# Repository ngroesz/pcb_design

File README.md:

# pcb_design
circuit board designs

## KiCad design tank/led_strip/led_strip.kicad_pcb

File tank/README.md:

# tank tank tank
Tank!

## Pixart camera
The turret board requires a Pixart camera. This component cannot be purchased off-the-shelf. Others pioneered the reusage of this module and plenty of documentation exists on the Internet. The camera modules are sourced from Wii Remotes, which can still (as of 2021) be sourced from eBay for fairly cheap. Search for "Wii Remote For Parts". They can be found individually or in lots, they shouldn't be much more than $5/controller. Make sure they are original Wii Remotes, not third-party copies nor "Wii Motion Plus". The camera module is fairly easy to desolder, though take care to not pull the contacts from the module when removing from the board. There are a couple other cool bits on a Wii Remote board, including a vibration motor and a beefy capacitor. These days, though I tend to just pull the camera module and throw away the rest.

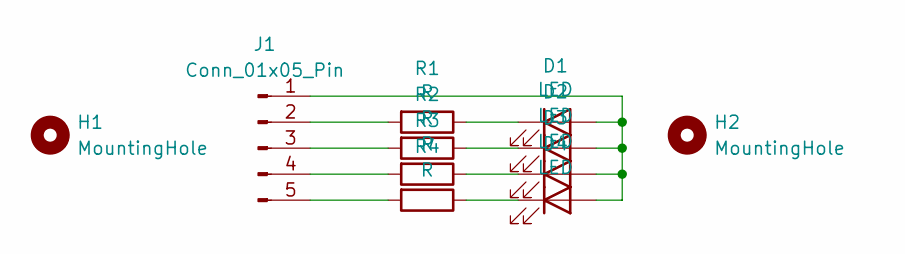
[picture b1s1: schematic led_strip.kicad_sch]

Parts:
D1, D2, D3, D4: LED; LED_D5.0mm
H1, H2: MountingHole; MountingHole_2.2mm_M2
J1: Conn_01x05_Pin; JST_XH_B5B-XH-A_1x05_P2.50mm_Vertical
R1, R2, R3, R4: R; R_Axial_DIN0207_L6.3mm_D2.5mm_P7.62mm_Horizontal

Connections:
unnamed: D1.2 (A), D2.2 (A), D3.2 (A), D4.2 (A), J1.1
unnamed: D1.1 (K), R1.1
unnamed: D2.1 (K), R2.1
unnamed: D3.1 (K), R3.1
unnamed: D4.1 (K), R4.1
unnamed: J1.2, R1.2
unnamed: J1.3, R2.2
unnamed: J1.4, R3.2
unnamed: J1.5, R4.2

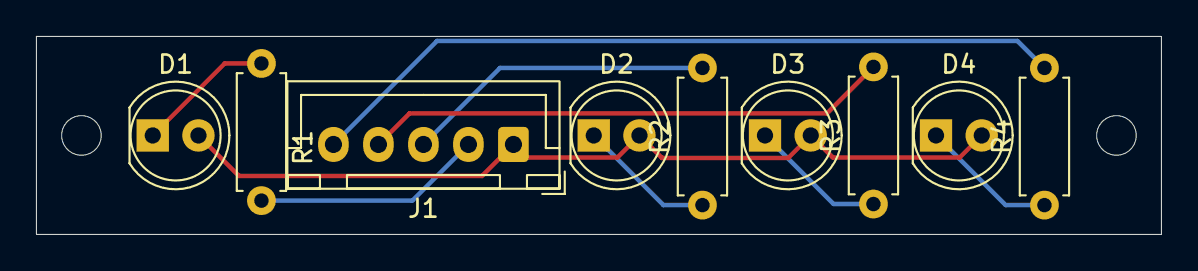
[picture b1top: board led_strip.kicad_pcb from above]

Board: 2 copper layers, 62.5 x 11.0 mm, 11 parts (0 on the bottom side), 9 nets.

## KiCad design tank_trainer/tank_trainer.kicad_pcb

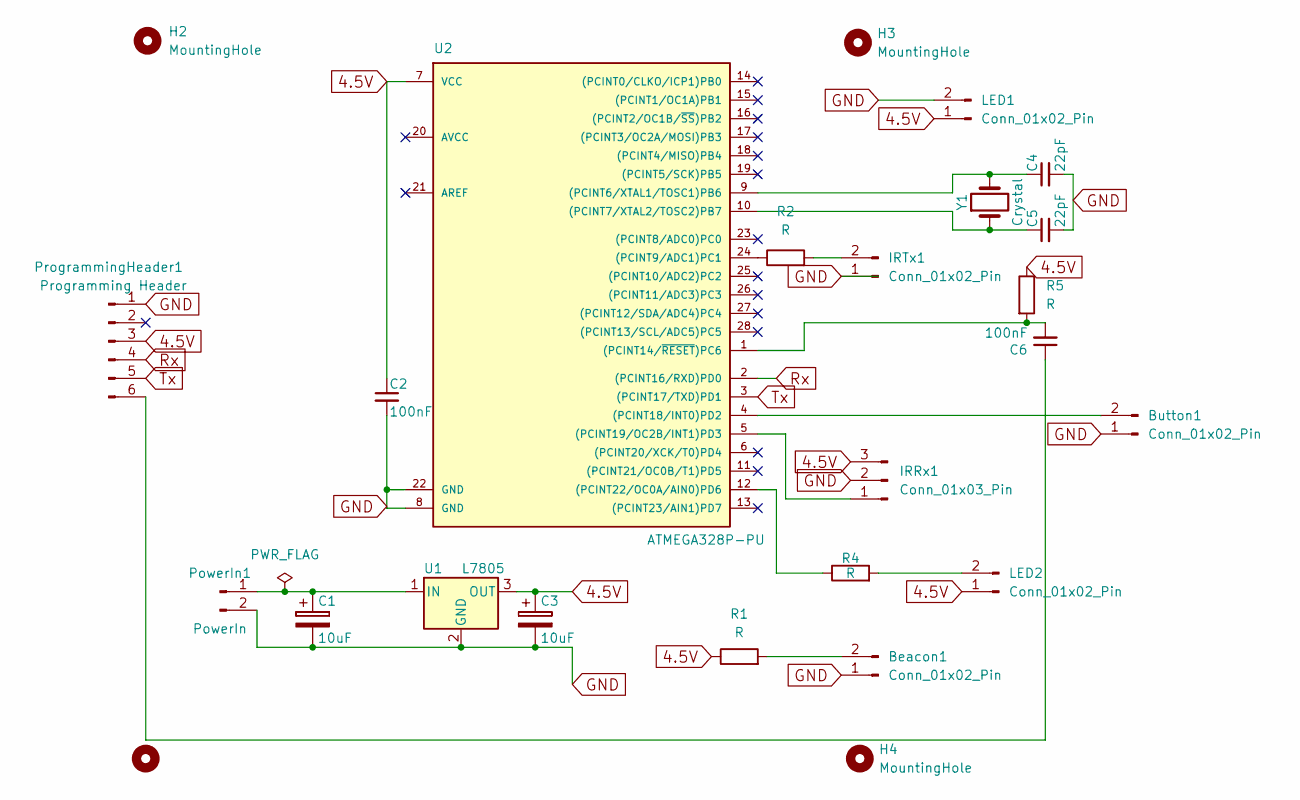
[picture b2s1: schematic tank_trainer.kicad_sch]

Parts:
Beacon1: Conn_01x02_Pin; JST_EH_B2B-EH-A_1x02_P2.50mm_Vertical
Button1: Conn_01x02_Pin; JST_EH_B2B-EH-A_1x02_P2.50mm_Vertical
C1, C3: 10uF; CP_Radial_D4.0mm_P2.00mm
C2, C6: 100nF; C_Disc_D5.0mm_W2.5mm_P2.50mm
C4, C5: 22pF; C_Disc_D5.0mm_W2.5mm_P2.50mm
H1, H2, H3, H4: MountingHole; MountingHole_3mm
IRRx1: Conn_01x03_Pin; JST_EH_B3B-EH-A_1x03_P2.50mm_Vertical
IRTx1: Conn_01x02_Pin; JST_EH_B2B-EH-A_1x02_P2.50mm_Vertical
LED1, LED2: Conn_01x02_Pin; JST_EH_B2B-EH-A_1x02_P2.50mm_Vertical
PowerIn1: PowerIn; JST_EH_B2B-EH-A_1x02_P2.50mm_Vertical
ProgrammingHeader1: Programming Header; PinHeader_1x06_P2.54mm_Horizontal
R1, R2, R4, R5: R; R_Axial_DIN0207_L6.3mm_D2.5mm_P7.62mm_Horizontal
U1: L7805; L7805CV
U2: ATMEGA328P-PU; DIP-28_W7.62mm
Y1: Crystal; Crystal_HC49-U_Vertical

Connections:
4.5V: C2.1, C3.1, IRRx1.3, LED1.1, LED2.1, ProgrammingHeader1.3, R1.1, R5.1, U1.3 (OUT), U2.7 (VCC)
GND: Beacon1.1, Button1.1, C1.2, C2.2, C3.2, C4.2, C5.2, IRRx1.2, IRTx1.1, LED1.2, PowerIn1.2, ProgrammingHeader1.1, U1.2 (GND), U2.8 (GND), U2.22 (GND)
unnamed: Beacon1.2, R1.2
unnamed: Button1.2, U2.4 ((PCINT18/INT0)PD2)
unnamed: IRRx1.1, U2.5 ((PCINT19/OC2B/INT1)PD3)
unnamed: IRTx1.2, R2.2
unnamed: LED2.2, R4.2
unnamed: C1.1, PowerIn1.1, U1.1 (IN)
unnamed: C6.1, ProgrammingHeader1.6
unnamed: C4.1, U2.9 ((PCINT6/XTAL1/TOSC1)PB6), Y1.2
unnamed: C5.1, U2.10 ((PCINT7/XTAL2/TOSC2)PB7), Y1.1
unnamed: R2.1, U2.24 ((PCINT9/ADC1)PC1)
unnamed: C6.2, R5.2, U2.1 ((PCINT14/~RESET)PC6)
unnamed: R4.1, U2.12 ((PCINT22/OC0A/AIN0)PD6)
Rx: ProgrammingHeader1.4, U2.2 ((PCINT16/RXD)PD0)
Tx: ProgrammingHeader1.5, U2.3 ((PCINT17/TXD)PD1)

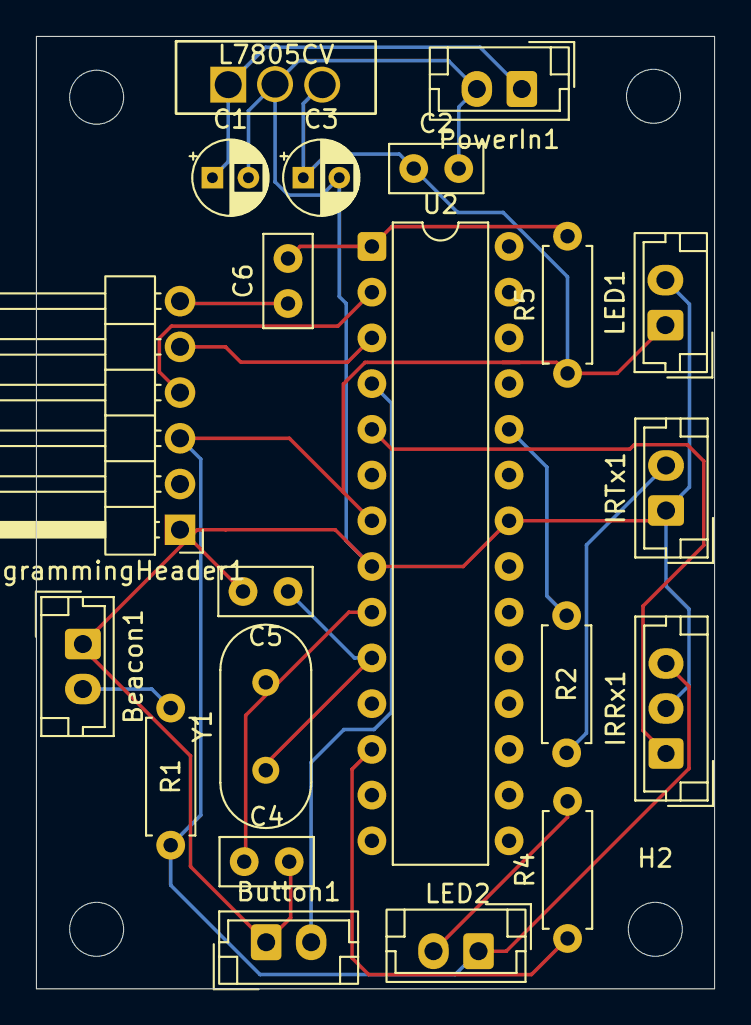
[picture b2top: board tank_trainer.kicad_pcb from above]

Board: 2 copper layers, 37.7 x 52.9 mm, 25 parts (0 on the bottom side), 16 nets.

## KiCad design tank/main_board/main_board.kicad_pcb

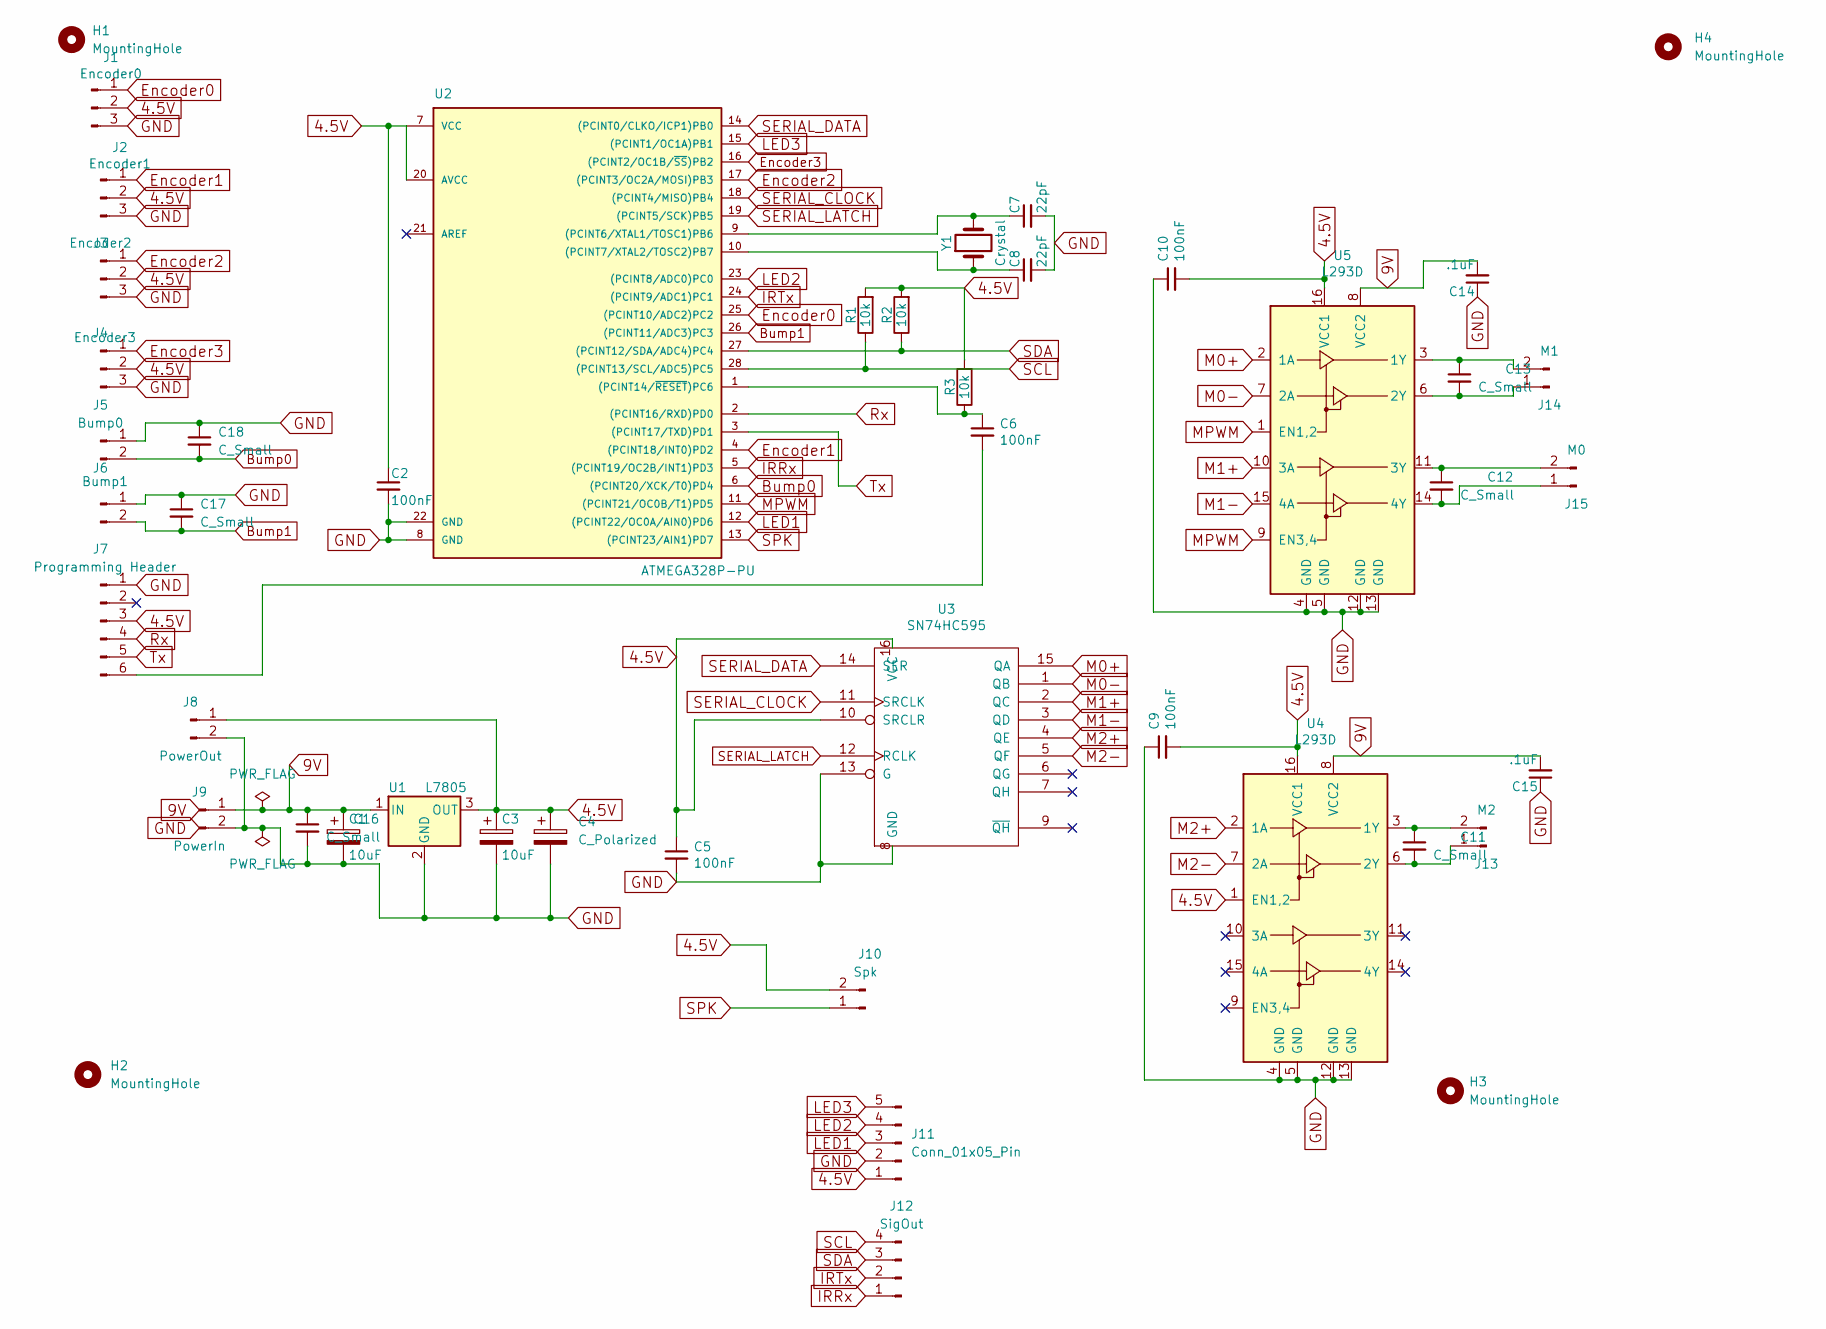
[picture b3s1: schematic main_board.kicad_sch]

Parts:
C1, C3: 10uF; CP_Radial_D4.0mm_P2.00mm
C2, C5, C6, C9, C10: 100nF; C_Disc_D5.0mm_W2.5mm_P2.50mm
C4: C_Polarized; CP_Radial_D6.3mm_P2.50mm
C7, C8: 22pF; C_Disc_D5.0mm_W2.5mm_P2.50mm
C11, C12, C13, C16, C17, C18: C_Small; C_Disc_D5.0mm_W2.5mm_P2.50mm
C14, C15: .1uF; C_Disc_D5.0mm_W2.5mm_P2.50mm
H1, H2, H3, H4: MountingHole; MountingHole_3mm
J1: Encoder0; JST_EH_B3B-EH-A_1x03_P2.50mm_Vertical
J2: Encoder1; JST_EH_B3B-EH-A_1x03_P2.50mm_Vertical
J3: Encoder2; JST_EH_B3B-EH-A_1x03_P2.50mm_Vertical
J4: Encoder3; JST_EH_B3B-EH-A_1x03_P2.50mm_Vertical
J5: Bump0; JST_EH_B2B-EH-A_1x02_P2.50mm_Vertical
J6: Bump1; JST_EH_B2B-EH-A_1x02_P2.50mm_Vertical
J7: Programming Header; PinHeader_1x06_P2.54mm_Horizontal
J8: PowerOut; JST_EH_B2B-EH-A_1x02_P2.50mm_Vertical
J9: PowerIn; TerminalBlock_Phoenix_PT-1,5-2-3.5-H_1x02_P3.50mm_Horizontal
J10: Spk; JST_EH_B2B-EH-A_1x02_P2.50mm_Vertical
J11: Conn_01x05_Pin; JST_EH_B5B-EH-A_1x05_P2.50mm_Vertical
J12: SigOut; JST_EH_B4B-EH-A_1x04_P2.50mm_Vertical
J13: M2; TerminalBlock_Phoenix_PT-1,5-2-3.5-H_1x02_P3.50mm_Horizontal
J14: M1; TerminalBlock_Phoenix_PT-1,5-2-3.5-H_1x02_P3.50mm_Horizontal
J15: M0; TerminalBlock_Phoenix_PT-1,5-2-3.5-H_1x02_P3.50mm_Horizontal
R1, R2, R3: 10k; R_Axial_DIN0207_L6.3mm_D2.5mm_P7.62mm_Horizontal
U1: L7805; L7805CV
U2: ATMEGA328P-PU; DIP-28_W7.62mm
U3: SN74HC595; DIP-16_W7.62mm
U4, U5: L293D; DIP-16_W7.62mm
Y1: Crystal; Crystal_HC49-U_Vertical

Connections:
4.5V: C2.1, C3.1, C4.1, C5.1, C9.2, C10.2, J1.2, J2.2, J3.2, J4.2, J7.3, J8.1, J10.2, J11.1, R1.2, R2.2, R3.2, U1.3 (OUT), U2.7 (VCC), U2.20 (AVCC), U3.10 (SRCLR), U3.16 (VCC), U4.1 (EN1,2), U4.16 (VCC1), U5.16 (VCC1)
9V: C1.1, C14.2, C15.2, C16.1, J9.1, U1.1 (IN), U4.8 (VCC2), U5.8 (VCC2)
Bump0: C18.2, J5.2, U2.6 ((PCINT20/XCK/T0)PD4)
Bump1: C17.2, J6.2, U2.26 ((PCINT11/ADC3)PC3)
Encoder0: J1.1, U2.25 ((PCINT10/ADC2)PC2)
Encoder1: J2.1, U2.4 ((PCINT18/INT0)PD2)
Encoder2: J3.1, U2.17 ((PCINT3/OC2A/MOSI)PB3)
Encoder3: J4.1, U2.16 ((PCINT2/OC1B/~SS)PB2)
GND: C1.2, C2.2, C3.2, C4.2, C5.2, C7.2, C8.2, C9.1, C10.1, C14.1, C15.1, C16.2, C17.1, C18.1, J1.3, J2.3, J3.3, J4.3, J5.1, J6.1, J7.1, J8.2, J9.2, J11.2, U1.2 (GND), U2.8 (GND), U2.22 (GND), U3.8 (GND), U3.13 (G), U4.4 (GND), U4.5 (GND), U4.12 (GND), U4.13 (GND), U5.4 (GND), U5.5 (GND), U5.12 (GND), U5.13 (GND)
IRRx: J12.1, U2.5 ((PCINT19/OC2B/INT1)PD3)
IRTx: J12.2, U2.24 ((PCINT9/ADC1)PC1)
LED1: J11.3, U2.12 ((PCINT22/OC0A/AIN0)PD6)
LED2: J11.4, U2.23 ((PCINT8/ADC0)PC0)
LED3: J11.5, U2.15 ((PCINT1/OC1A)PB1)
M0+: U3.15 (QA), U5.2 (1A)
M0-: U3.1 (QB), U5.7 (2A)
M1+: U3.2 (QC), U5.10 (3A)
M1-: U3.3 (QD), U5.15 (4A)
M2+: U3.4 (QE), U4.2 (1A)
M2-: U3.5 (QF), U4.7 (2A)
MPWM: U2.11 ((PCINT21/OC0B/T1)PD5), U5.1 (EN1,2), U5.9 (EN3,4)
unnamed: C6.2, J7.6
unnamed: C11.2, J13.1, U4.6 (2Y)
unnamed: C11.1, J13.2, U4.3 (1Y)
unnamed: C13.2, J14.1, U5.6 (2Y)
unnamed: C13.1, J14.2, U5.3 (1Y)
unnamed: C12.2, J15.1, U5.14 (4Y)
unnamed: C12.1, J15.2, U5.11 (3Y)
unnamed: C7.1, U2.9 ((PCINT6/XTAL1/TOSC1)PB6), Y1.2
unnamed: C8.1, U2.10 ((PCINT7/XTAL2/TOSC2)PB7), Y1.1
unnamed: C6.1, R3.1, U2.1 ((PCINT14/~RESET)PC6)
Rx: J7.4, U2.2 ((PCINT16/RXD)PD0)
SCL: J12.4, R1.1, U2.28 ((PCINT13/SCL/ADC5)PC5)
SDA: J12.3, R2.1, U2.27 ((PCINT12/SDA/ADC4)PC4)
SERIAL_CLOCK: U2.18 ((PCINT4/MISO)PB4), U3.11 (SRCLK)
SERIAL_DATA: U2.14 ((PCINT0/CLKO/ICP1)PB0), U3.14 (SER)
SERIAL_LATCH: U2.19 ((PCINT5/SCK)PB5), U3.12 (RCLK)
SPK: J10.1, U2.13 ((PCINT23/AIN1)PD7)
Tx: J7.5, U2.3 ((PCINT17/TXD)PD1)

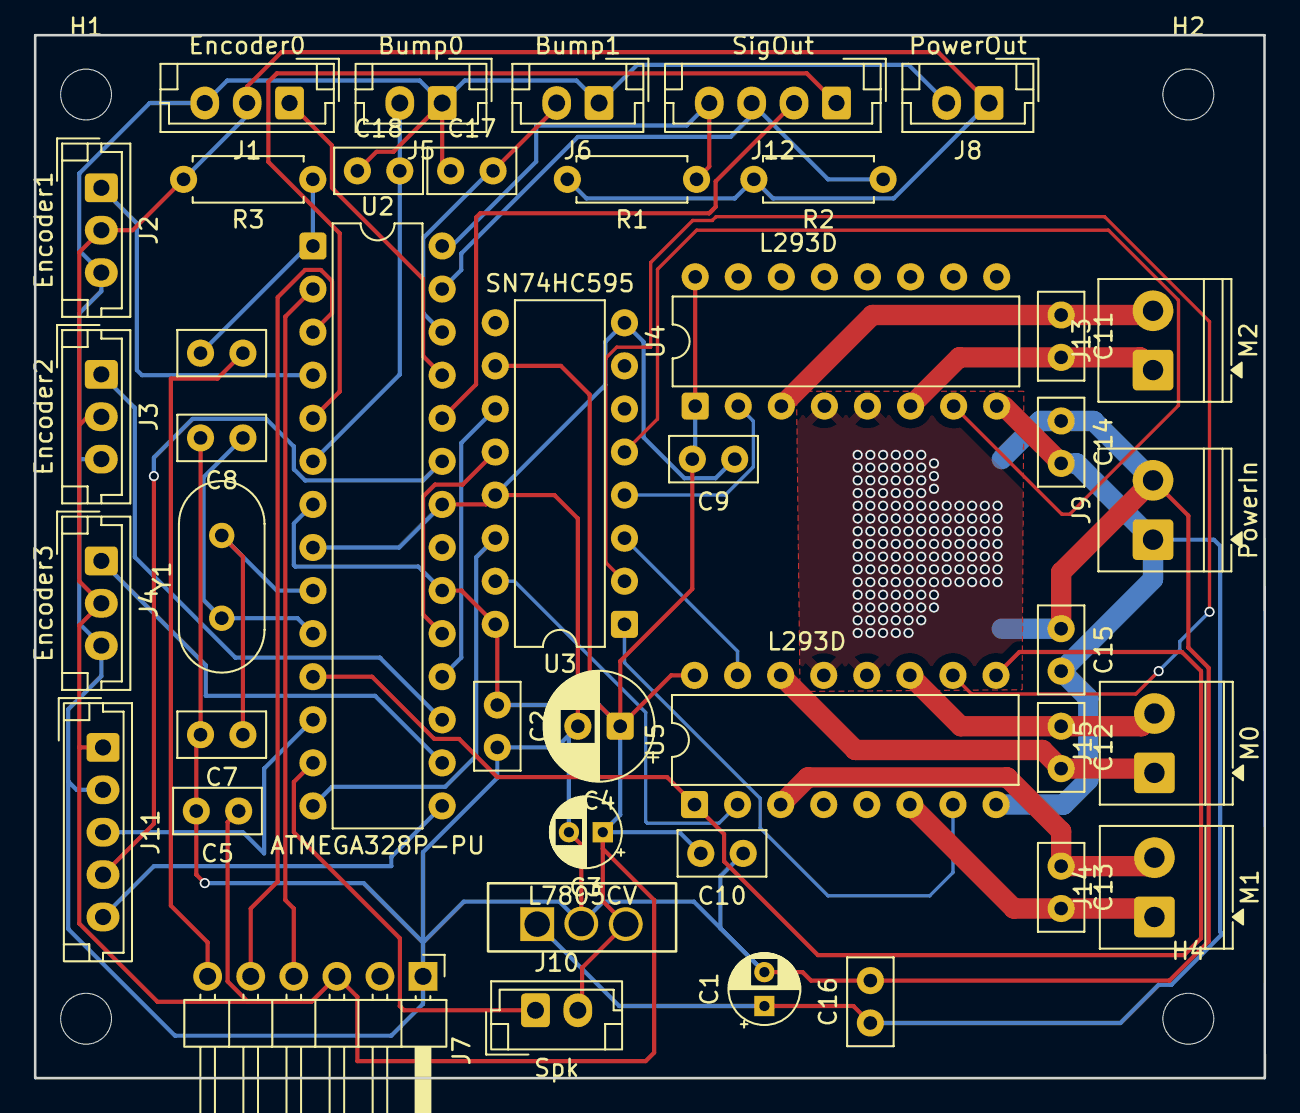
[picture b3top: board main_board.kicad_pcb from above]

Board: 2 copper layers, 72.5 x 61.5 mm, 46 parts (0 on the bottom side), 39 nets.

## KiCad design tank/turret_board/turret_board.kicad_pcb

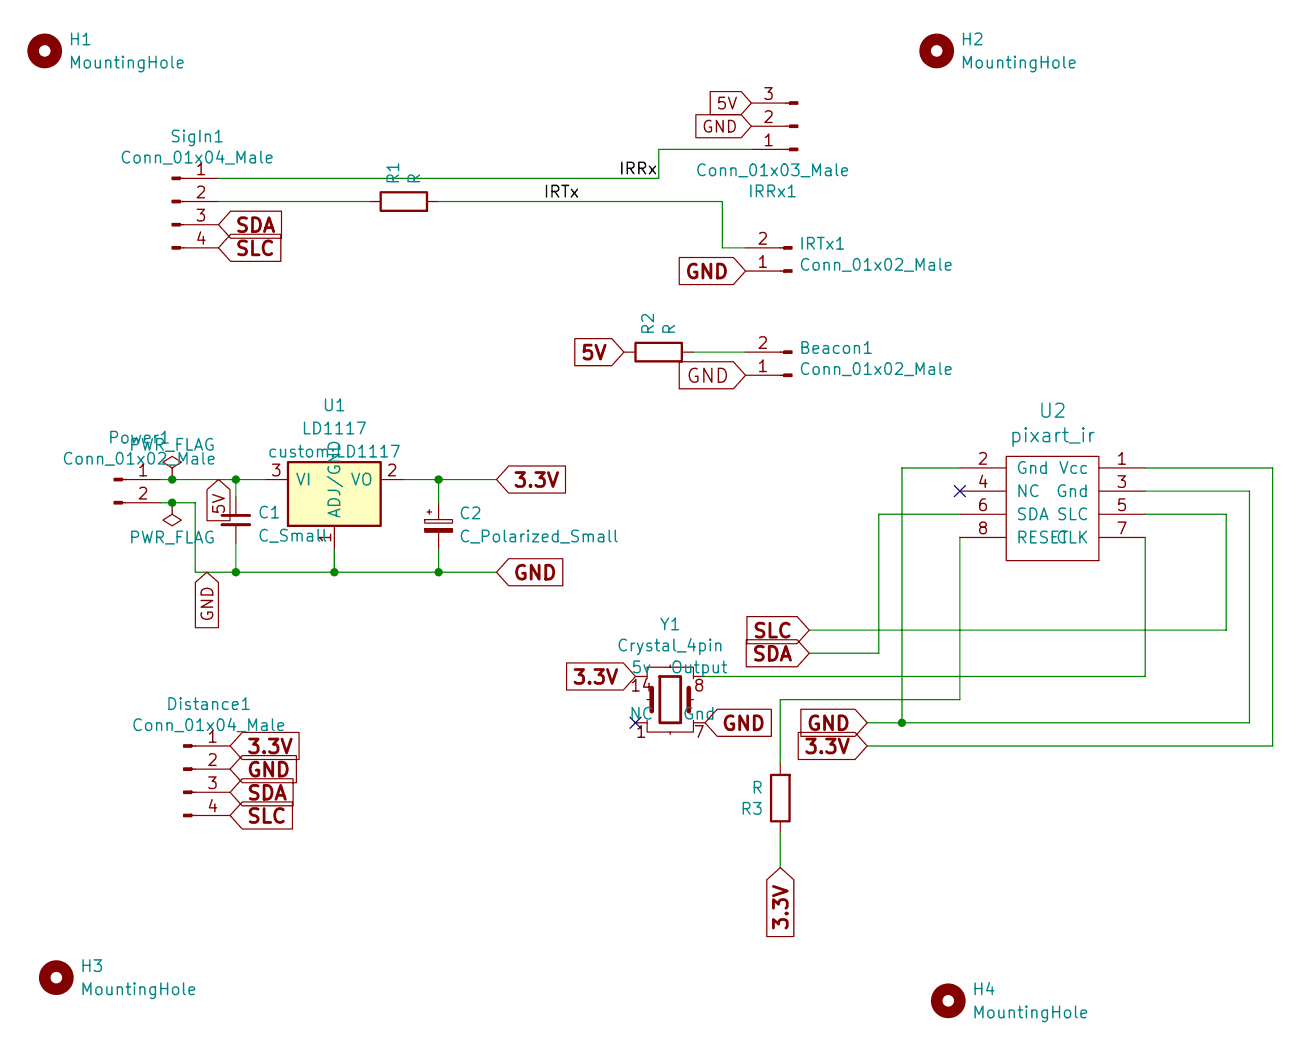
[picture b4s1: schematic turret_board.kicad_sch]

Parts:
Beacon1: Conn_01x02_Male; JST_EH_B2B-EH-A_1x02_P2.50mm_Vertical
C1: C_Small; CP_Radial_D4.0mm_P2.00mm
C2: C_Polarized_Small; C_Disc_D4.7mm_W2.5mm_P5.00mm
Distance1: Conn_01x04_Male; JST_EH_B4B-EH-A_1x04_P2.50mm_Vertical
H1, H2, H3, H4: MountingHole; MountingHole_2.2mm_M2
IRRx1: Conn_01x03_Male; JST_EH_B3B-EH-A_1x03_P2.50mm_Vertical
IRTx1: Conn_01x02_Male; JST_EH_B2B-EH-A_1x02_P2.50mm_Vertical
Power1: Conn_01x02_Male; JST_EH_B2B-EH-A_1x02_P2.50mm_Vertical
R1, R2, R3: R; R_Axial_DIN0207_L6.3mm_D2.5mm_P7.62mm_Horizontal
SigIn1: Conn_01x04_Male; JST_EH_B4B-EH-A_1x04_P2.50mm_Vertical
U1: LD1117
U2: pixart_ir
Y1: Crystal_4pin; ECS-100AX

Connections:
3.3V: C2.1, Distance1.1, R3.1, U1.2 (VO), U2.1 (Vcc), Y1.14 (5v)
5V: C1.1, IRRx1.3, Power1.1, R2.1, U1.3 (VI)
/IRRx: IRRx1.1, SigIn1.1
/IRTx: IRTx1.2, R1.2
GND: Beacon1.1, C1.2, C2.2, Distance1.2, IRRx1.2, IRTx1.1, Power1.2, U1.1 (ADJ/GND), U2.2 (Gnd), U2.3 (Gnd), Y1.7 (Gnd)
unnamed: Beacon1.2, R2.2
unnamed: R1.1, SigIn1.2
unnamed: U2.7 (CLK), Y1.8 (Output)
unnamed: R3.2, U2.8 (RESET)
SDA: Distance1.3, SigIn1.3, U2.6 (SDA)
SLC: Distance1.4, SigIn1.4, U2.5 (SLC)

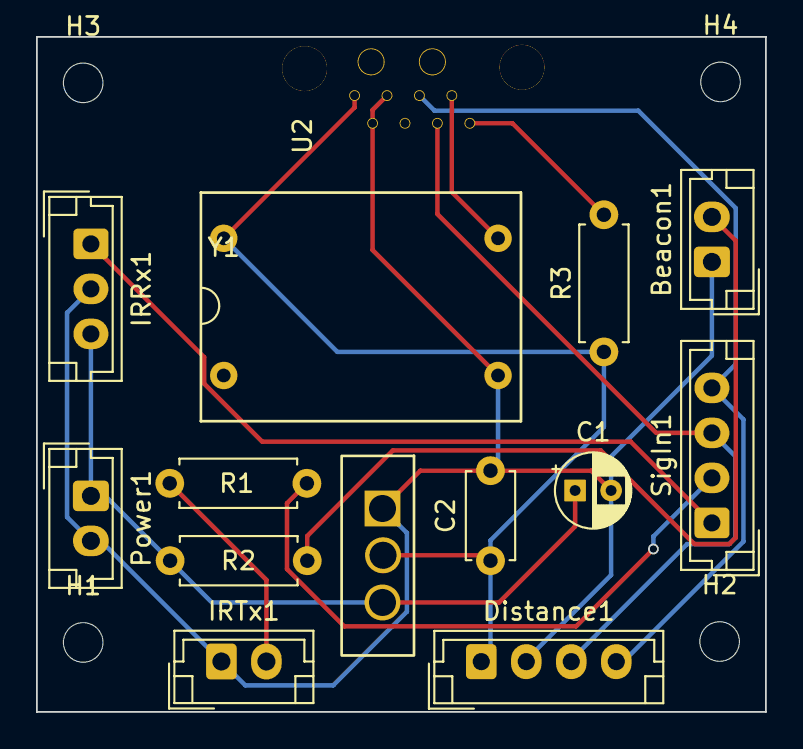
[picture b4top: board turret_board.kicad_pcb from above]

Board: 2 copper layers, 40.5 x 37.5 mm, 18 parts (0 on the bottom side), 11 nets.

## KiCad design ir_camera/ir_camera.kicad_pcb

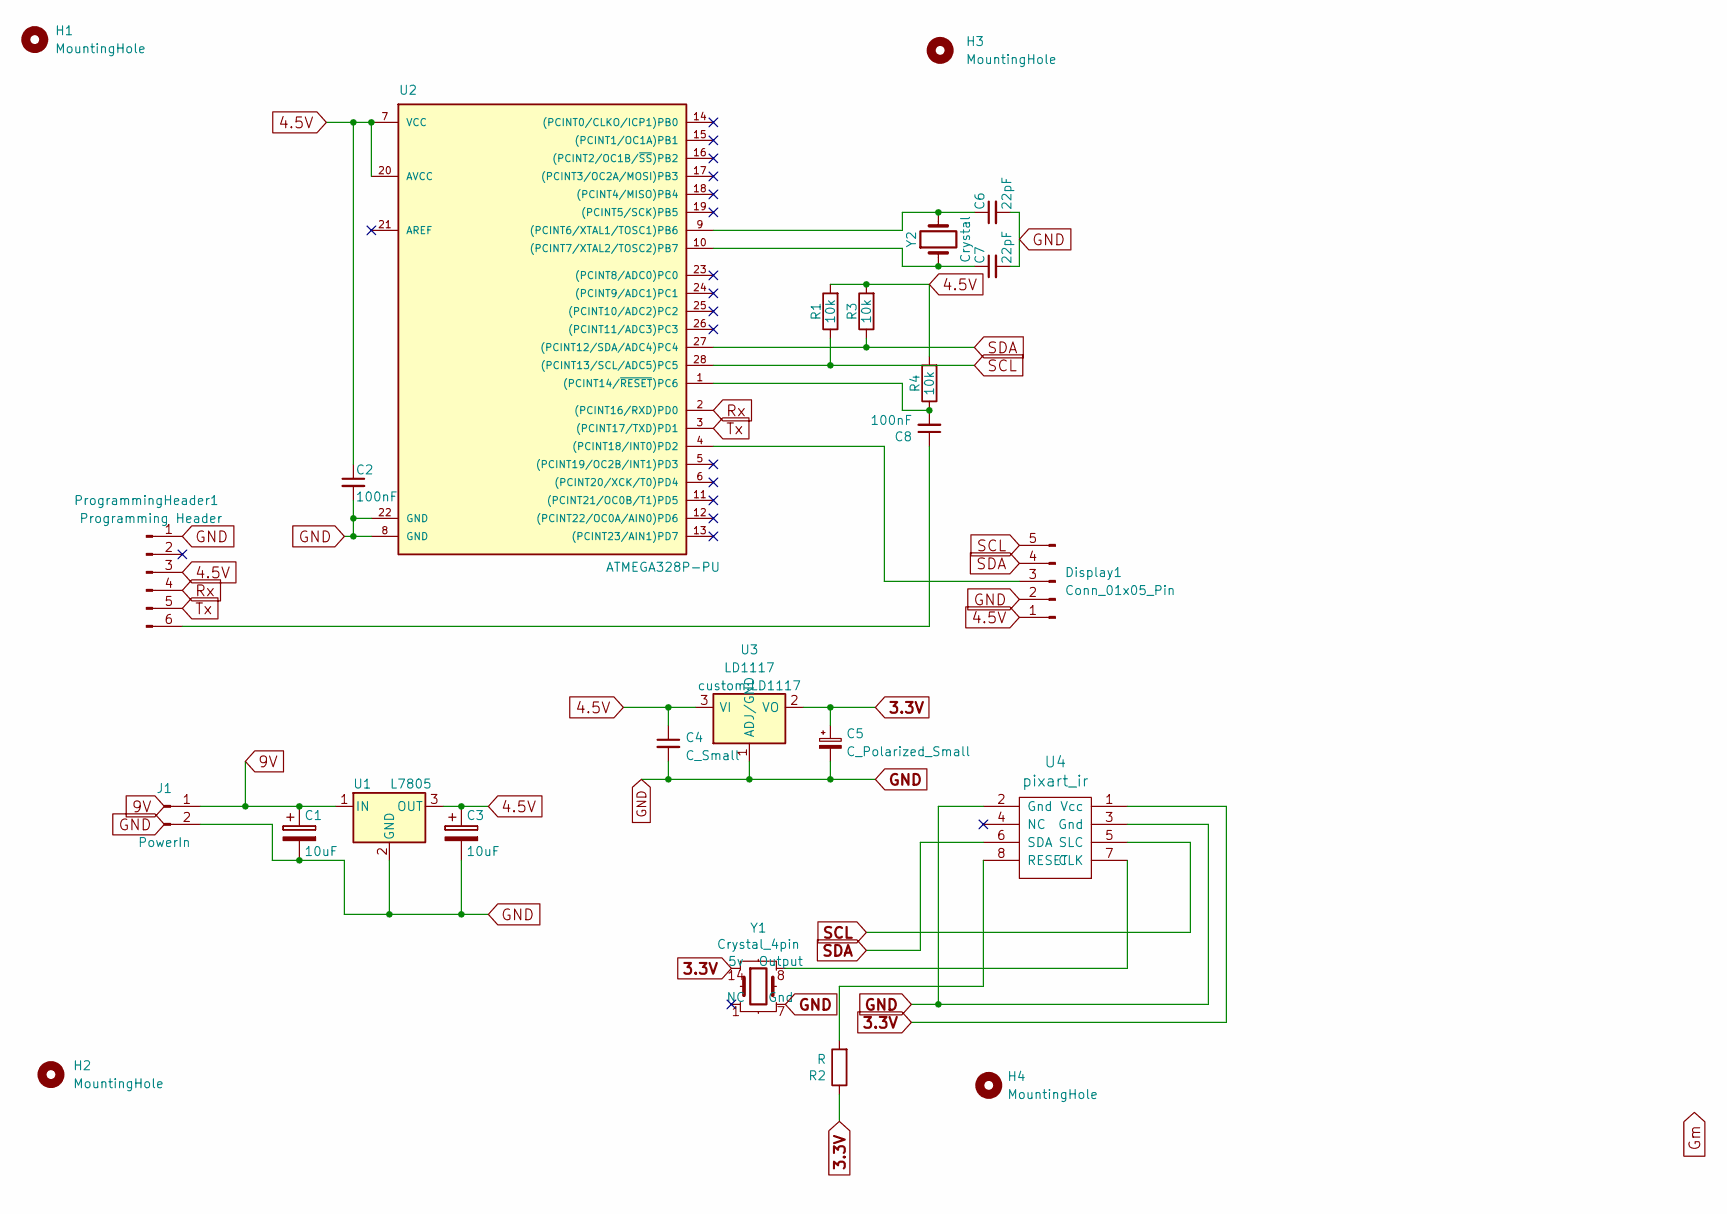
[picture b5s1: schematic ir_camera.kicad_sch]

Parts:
C1, C3: 10uF; CP_Radial_D4.0mm_P2.00mm
C2, C8: 100nF; C_Disc_D5.0mm_W2.5mm_P2.50mm
C4: C_Small; CP_Radial_D4.0mm_P2.00mm
C5: C_Polarized_Small; C_Disc_D4.7mm_W2.5mm_P5.00mm
C6, C7: 22pF; C_Disc_D5.0mm_W2.5mm_P2.50mm
Display1: Conn_01x05_Pin; JST_EH_B5B-EH-A_1x05_P2.50mm_Vertical
H1, H2, H3, H4: MountingHole; MountingHole_3mm
J1: PowerIn; JST_EH_B2B-EH-A_1x02_P2.50mm_Vertical
ProgrammingHeader1: Programming Header; PinHeader_1x06_P2.54mm_Horizontal
R1, R3, R4: 10k; R_Axial_DIN0207_L6.3mm_D2.5mm_P7.62mm_Horizontal
R2: R; R_Axial_DIN0207_L6.3mm_D2.5mm_P7.62mm_Horizontal
U1: L7805; L7805CV
U2: ATMEGA328P-PU; DIP-28_W7.62mm
U3: LD1117
U4: pixart_ir
Y1: Crystal_4pin; ECS-100AX
Y2: Crystal; Crystal_HC49-U_Vertical

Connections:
3.3V: C5.1, R2.1, U3.2 (VO), U4.1 (Vcc), Y1.14 (5v)
4.5V: C2.1, C3.1, C4.1, Display1.1, ProgrammingHeader1.3, R1.2, R3.2, R4.2, U1.3 (OUT), U2.7 (VCC), U2.20 (AVCC), U3.3 (VI)
9V: C1.1, J1.1, U1.1 (IN)
GND: C1.2, C2.2, C3.2, C4.2, C5.2, C6.2, C7.2, Display1.2, J1.2, ProgrammingHeader1.1, U1.2 (GND), U2.8 (GND), U2.22 (GND), U3.1 (ADJ/GND), U4.2 (Gnd), U4.3 (Gnd), Y1.7 (Gnd)
unnamed: Display1.3, U2.4 ((PCINT18/INT0)PD2)
unnamed: C8.1, ProgrammingHeader1.6
unnamed: C6.1, U2.9 ((PCINT6/XTAL1/TOSC1)PB6), Y2.2
unnamed: C7.1, U2.10 ((PCINT7/XTAL2/TOSC2)PB7), Y2.1
unnamed: C8.2, R4.1, U2.1 ((PCINT14/~RESET)PC6)
unnamed: U4.7 (CLK), Y1.8 (Output)
unnamed: R2.2, U4.8 (RESET)
Rx: ProgrammingHeader1.4, U2.2 ((PCINT16/RXD)PD0)
SCL: Display1.5, R1.1, U2.28 ((PCINT13/SCL/ADC5)PC5), U4.5 (SLC)
SDA: Display1.4, R3.1, U2.27 ((PCINT12/SDA/ADC4)PC4), U4.6 (SDA)
Tx: ProgrammingHeader1.5, U2.3 ((PCINT17/TXD)PD1)

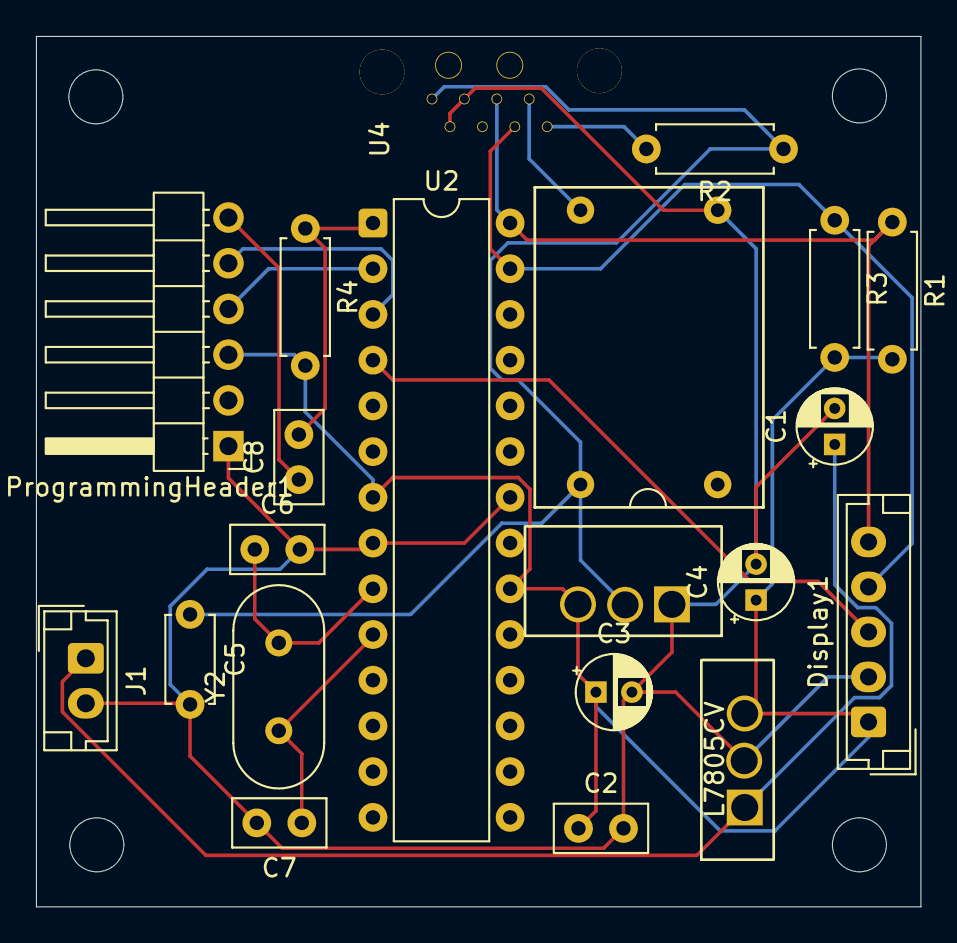
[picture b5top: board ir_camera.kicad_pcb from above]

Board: 2 copper layers, 49.1 x 48.4 mm, 25 parts (0 on the bottom side), 15 nets.

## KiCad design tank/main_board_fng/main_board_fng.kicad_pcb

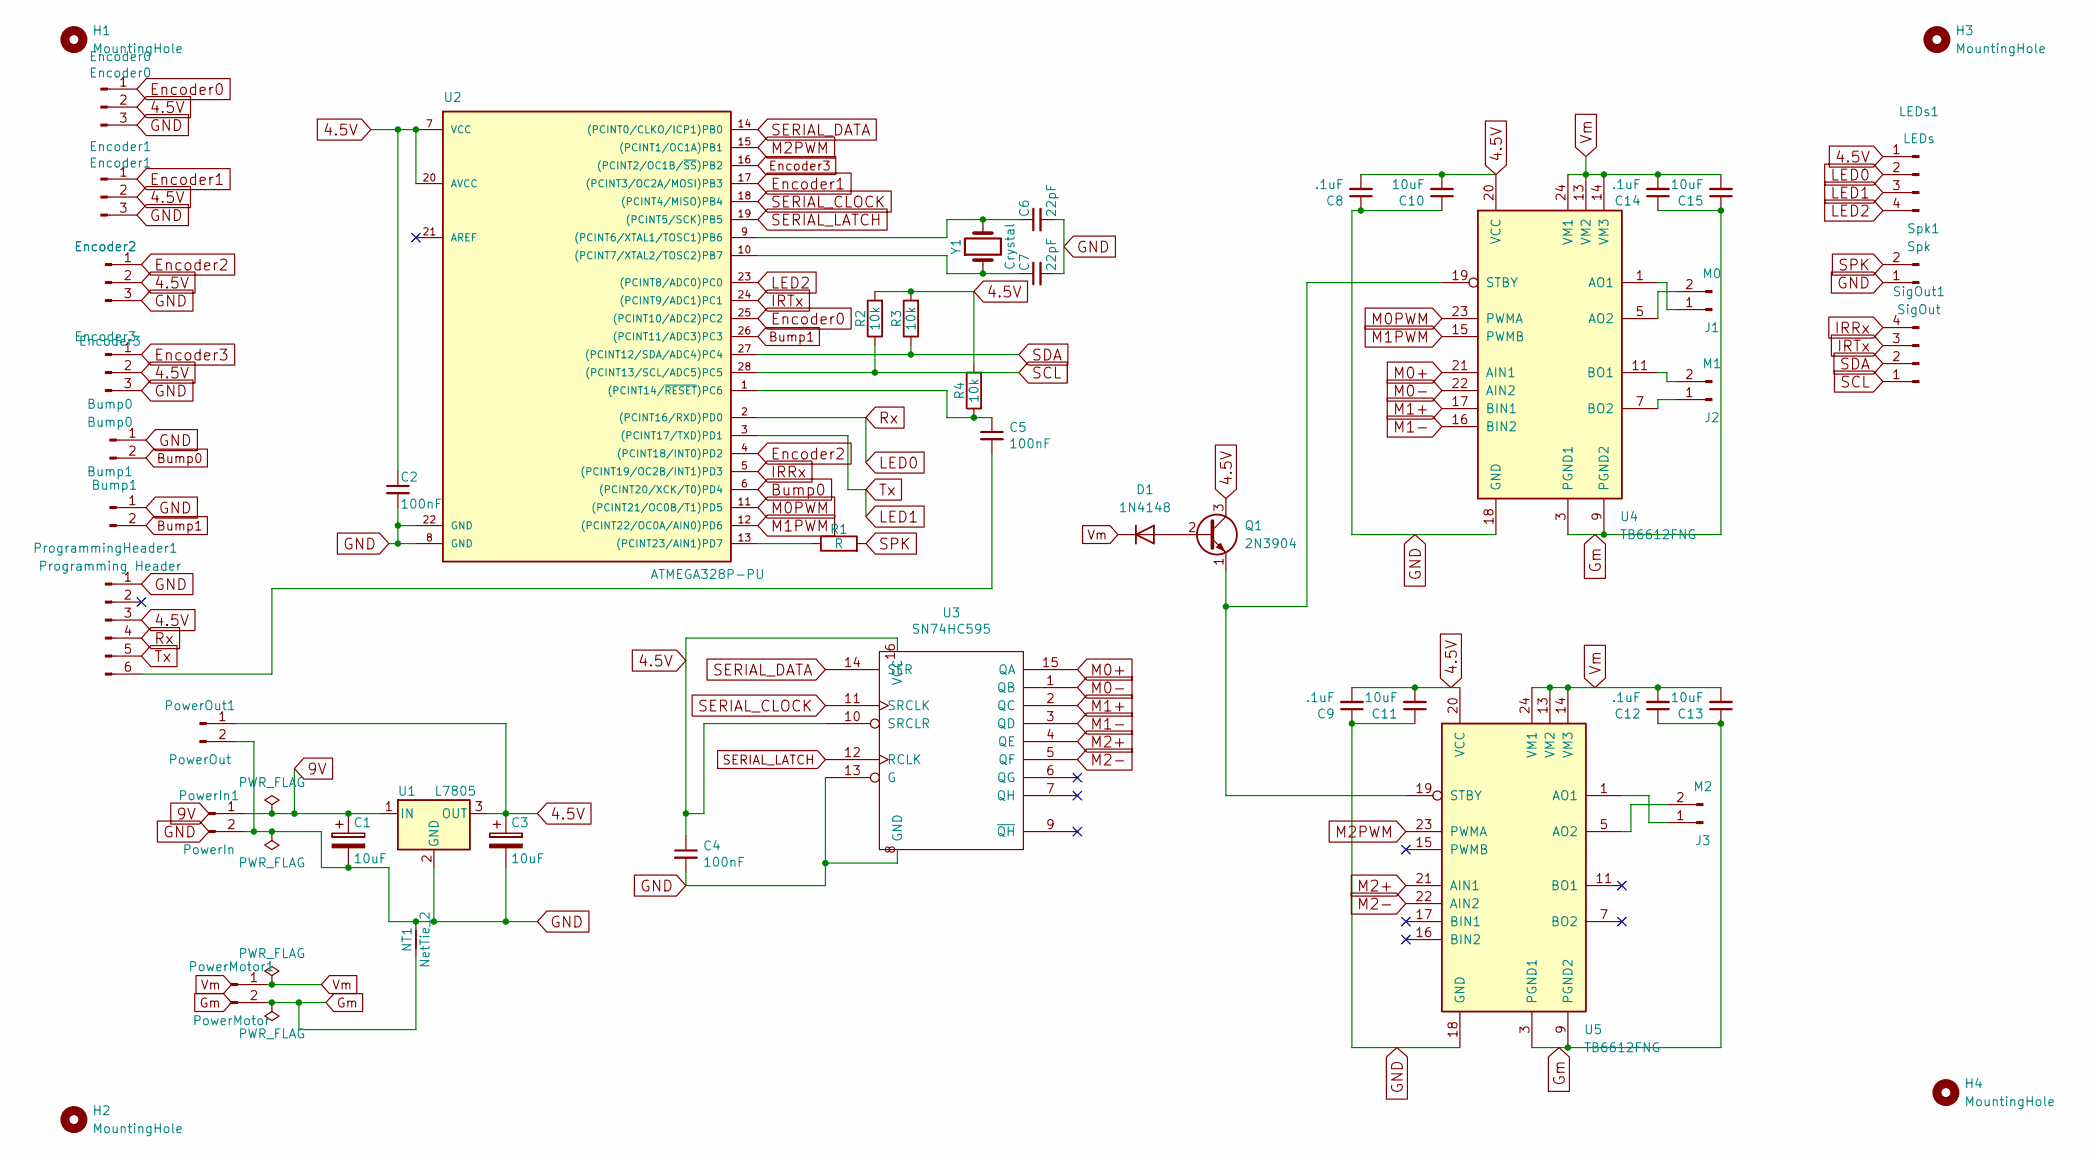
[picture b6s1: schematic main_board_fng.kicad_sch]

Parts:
Bump0: Bump0; JST_EH_B2B-EH-A_1x02_P2.50mm_Vertical
Bump1: Bump1; JST_EH_B2B-EH-A_1x02_P2.50mm_Vertical
C1, C3, C10, C11, C13, C15: 10uF; CP_Radial_D4.0mm_P2.00mm
C2, C4, C5: 100nF; C_Disc_D5.0mm_W2.5mm_P2.50mm
C6, C7: 22pF; C_Disc_D5.0mm_W2.5mm_P2.50mm
C8, C9, C12, C14: .1uF; C_Disc_D5.0mm_W2.5mm_P2.50mm
D1: 1N4148; D_DO-15_P5.08mm_Vertical_AnodeUp
Encoder0: Encoder0; JST_EH_B3B-EH-A_1x03_P2.50mm_Vertical
Encoder1: Encoder1; JST_EH_B3B-EH-A_1x03_P2.50mm_Vertical
Encoder2: Encoder2; JST_EH_B3B-EH-A_1x03_P2.50mm_Vertical
Encoder3: Encoder3; JST_EH_B3B-EH-A_1x03_P2.50mm_Vertical
H1, H2, H3, H4: MountingHole; MountingHole_3mm
J1: M0; TerminalBlock_Phoenix_PT-1,5-2-3.5-H_1x02_P3.50mm_Horizontal
J2: M1; TerminalBlock_Phoenix_PT-1,5-2-3.5-H_1x02_P3.50mm_Horizontal
J3: M2; TerminalBlock_Phoenix_PT-1,5-2-3.5-H_1x02_P3.50mm_Horizontal
LEDs1: LEDs; JST_EH_B4B-EH-A_1x04_P2.50mm_Vertical
NT1: NetTie_2; NetTie-2_THT_Pad0.3mm
PowerIn1: PowerIn; JST_EH_B2B-EH-A_1x02_P2.50mm_Vertical
PowerMotor1: PowerMotor; TerminalBlock_Phoenix_PT-1,5-2-3.5-H_1x02_P3.50mm_Horizontal
PowerOut1: PowerOut; JST_EH_B2B-EH-A_1x02_P2.50mm_Vertical
ProgrammingHeader1: Programming Header; PinHeader_1x06_P2.54mm_Vertical
Q1: 2N3904; TO-92_Inline
R1: R; R_Axial_DIN0207_L6.3mm_D2.5mm_P7.62mm_Horizontal
R2, R3, R4: 10k; R_Axial_DIN0207_L6.3mm_D2.5mm_P7.62mm_Horizontal
SigOut1: SigOut; JST_EH_B4B-EH-A_1x04_P2.50mm_Vertical
Spk1: Spk; JST_EH_B2B-EH-A_1x02_P2.50mm_Vertical
U1: L7805; L7805CV
U2: ATMEGA328P-PU; DIP-28_W7.62mm
U3: SN74HC595; DIP-16_W7.62mm
U4, U5: TB6612FNG; SSOP-24_5.3x8.2mm_P0.65mm
Y1: Crystal; Crystal_HC49-U_Vertical

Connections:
4.5V: C2.1, C3.1, C4.1, C8.2, C9.2, C10.2, C11.2, Encoder0.2, Encoder1.2, Encoder2.2, Encoder3.2, LEDs1.1, PowerOut1.1, ProgrammingHeader1.3, Q1.3 (C), R2.2, R3.2, R4.2, U1.3 (OUT), U2.7 (VCC), U2.20 (AVCC), U3.10 (SRCLR), U3.16 (VCC), U4.20 (VCC), U5.20 (VCC)
9V: C1.1, PowerIn1.1, U1.1 (IN)
Bump0: Bump0.2, U2.6 ((PCINT20/XCK/T0)PD4)
Bump1: Bump1.2, U2.26 ((PCINT11/ADC3)PC3)
Encoder0: Encoder0.1, U2.25 ((PCINT10/ADC2)PC2)
Encoder1: Encoder1.1, U2.17 ((PCINT3/OC2A/MOSI)PB3)
Encoder2: Encoder2.1, U2.4 ((PCINT18/INT0)PD2)
Encoder3: Encoder3.1, U2.16 ((PCINT2/OC1B/~SS)PB2)
GND: Bump0.1, Bump1.1, C1.2, C2.2, C3.2, C4.2, C6.2, C7.2, C8.1, C9.1, C10.1, C11.1, Encoder0.3, Encoder1.3, Encoder2.3, Encoder3.3, NT1.2, PowerIn1.2, PowerOut1.2, ProgrammingHeader1.1, Spk1.1, U1.2 (GND), U2.8 (GND), U2.22 (GND), U3.8 (GND), U3.13 (G), U4.18 (GND), U5.18 (GND)
Gm: C12.1, C13.1, C14.1, C15.1, NT1.1, PowerMotor1.2, U4.3 (PGND1), U4.4 (PGND1), U4.9 (PGND2), U4.10 (PGND2), U5.3 (PGND1), U5.4 (PGND1), U5.9 (PGND2), U5.10 (PGND2)
IRRx: SigOut1.4, U2.5 ((PCINT19/OC2B/INT1)PD3)
IRTx: SigOut1.3, U2.24 ((PCINT9/ADC1)PC1)
LED0: LEDs1.2, ProgrammingHeader1.4, U2.2 ((PCINT16/RXD)PD0)
LED1: LEDs1.3, ProgrammingHeader1.5, U2.3 ((PCINT17/TXD)PD1)
LED2: LEDs1.4, U2.23 ((PCINT8/ADC0)PC0)
M0+: U3.15 (QA), U4.21 (AIN1)
M0-: U3.1 (QB), U4.22 (AIN2)
M0PWM: U2.11 ((PCINT21/OC0B/T1)PD5), U4.23 (PWMA)
M1+: U3.2 (QC), U4.17 (BIN1)
M1-: U3.3 (QD), U4.16 (BIN2)
M1PWM: U2.12 ((PCINT22/OC0A/AIN0)PD6), U4.15 (PWMB)
M2+: U3.4 (QE), U5.21 (AIN1)
M2-: U3.5 (QF), U5.22 (AIN2)
M2PWM: U2.15 ((PCINT1/OC1A)PB1), U5.23 (PWMA)
unnamed: D1.2 (A), Q1.2 (B)
unnamed: J1.1, U4.1 (AO1), U4.2 (AO1)
unnamed: J1.2, U4.5 (AO2), U4.6 (AO2)
unnamed: J2.1, U4.7 (BO2), U4.8 (BO2)
unnamed: J2.2, U4.11 (BO1), U4.12 (BO1)
unnamed: J3.1, U5.1 (AO1), U5.2 (AO1)
unnamed: J3.2, U5.5 (AO2), U5.6 (AO2)
unnamed: C5.2, ProgrammingHeader1.6
unnamed: Q1.1 (E), U4.19 (STBY), U5.19 (STBY)
unnamed: C6.1, U2.9 ((PCINT6/XTAL1/TOSC1)PB6), Y1.2
unnamed: C7.1, U2.10 ((PCINT7/XTAL2/TOSC2)PB7), Y1.1
unnamed: C5.1, R4.1, U2.1 ((PCINT14/~RESET)PC6)
unnamed: R1.1, U2.13 ((PCINT23/AIN1)PD7)
SCL: R2.1, SigOut1.1, U2.28 ((PCINT13/SCL/ADC5)PC5)
SDA: R3.1, SigOut1.2, U2.27 ((PCINT12/SDA/ADC4)PC4)
SERIAL_CLOCK: U2.18 ((PCINT4/MISO)PB4), U3.11 (SRCLK)
SERIAL_DATA: U2.14 ((PCINT0/CLKO/ICP1)PB0), U3.14 (SER)
SERIAL_LATCH: U2.19 ((PCINT5/SCK)PB5), U3.12 (RCLK)
SPK: R1.2, Spk1.2
Vm: C12.2, C13.2, C14.2, C15.2, D1.1 (K), PowerMotor1.1, U4.13 (VM2), U4.14 (VM3), U4.24 (VM1), U5.13 (VM2), U5.14 (VM3), U5.24 (VM1)
